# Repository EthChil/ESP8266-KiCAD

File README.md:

# ESP8266-KiCAD
Latest gerbers are in the folder plots. The files for the PCB are either the gerbers in plot or the pcb file.

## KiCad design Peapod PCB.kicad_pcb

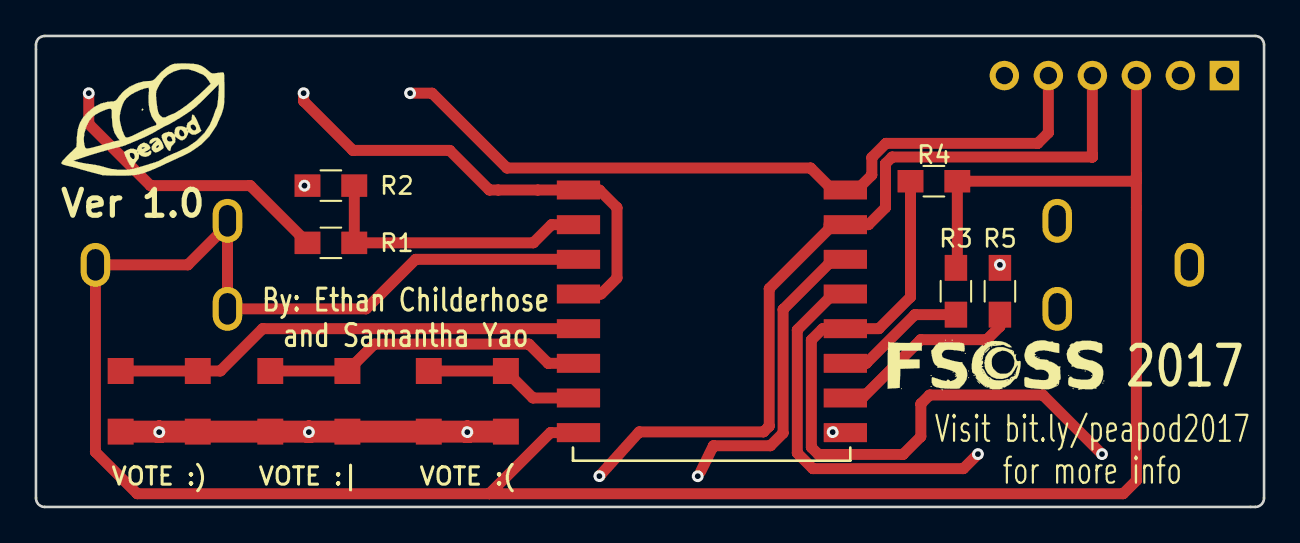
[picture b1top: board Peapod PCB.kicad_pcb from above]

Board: 2 copper layers, 70.9 x 27.2 mm, 18 parts (1 on the bottom side), 15 nets.

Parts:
ANALOG: CONN_01X01; Alligator Pad
BT1: Battery_Cell; BatteryMount
FTDI 3.3V: CONN_01X06; Pin_Header_Straight_1x06_Pitch2.54mm
GND   GPIO0: CONN_01X02; Bridge Pad
GPIO4, GPIO5: CONN_01X01; Alligator Pad
R1: 25k; R_0805_HandSoldering
R2, R3, R4, R5: 10k; R_0805_HandSoldering
RESET   GND: CONN_01X02; Bridge Pad
RX: CONN_01X01; Alligator Pad
TX: CONN_01X01; Alligator Pad
U1: ESP8266; ESP-12E_SMD
VOTE :(: Pushbutton
VOTE :): Pushbutton
VOTE :|: Pushbutton

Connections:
+3V3: BT1.1, FTDI 3.3V.3, R3.1, R4.2, U1.3, U1.8
GND: BT1.2, FTDI 3.3V.1, GND GPIO0.2, R2.2, R5.2, RESET GND.2, U1.9, VOTE :(.1, VOTE :).1, VOTE :|.1
unnamed: U1.6, VOTE :|.2
unnamed: U1.5, VOTE :).2
unnamed: U1.7, VOTE :(.2
unnamed: ANALOG.1, R1.2
unnamed: RESET GND.1, U1.1, U1.4
unnamed: FTDI 3.3V.4, RX.1, U1.15
unnamed: FTDI 3.3V.5, TX.1, U1.16
unnamed: GPIO5.1, U1.14
unnamed: GPIO4.1, U1.13
unnamed: GND GPIO0.1, R4.1, U1.12
unnamed: R1.1, R2.1, U1.2
unnamed: R3.2, U1.11
unnamed: R5.1, U1.10

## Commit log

2017-08-15 new KiCAD project
2017-08-15 Added bash files
2017-08-15 added button libs
2017-08-15 more libs
2017-08-15 deleted useless libs
2017-08-15 Added pushbutton
2017-08-15 Changed PushButton
2017-08-15 Updated PushButton
2017-08-15 finished schematic
2017-08-15 updated schematic
2017-08-15 Updated file
2017-08-15 Updated main file
2017-08-15 alligator pad done
2017-08-15 bridge pad made
2017-08-15 created battery mount
2017-08-16 assigned footprints
2017-08-16 finished assigning footprints to components
2017-08-16 fixed changes
2017-08-16 Changed Button
2017-08-16 centered footprints
2017-08-16 fixed battery mount
2017-08-16 Updated lib
2017-08-16 designing
2017-08-17 Changed main file for layout
2017-08-17 changed things
2017-08-17 made vias and tracks
2017-08-17 made fill zones
2017-08-17 fixed stuff
2017-08-17 Moved routing on the lines
2017-08-17 got rid of most vias
2017-08-17 Changed Via
2017-08-17 changed copper to back plate
2017-08-17 Changed schematic
2017-08-17 stuff
2017-08-17 stufff
2017-08-17 Added labels
2017-08-17 Updated tracks
2017-08-17 final??
2017-08-17 Made wire routes nicer
2017-08-17 looks nice
2017-08-17 Changed the routing again
2017-08-17 Changed one run
2017-08-17 Moved RX TX
2017-08-17 Moved RX TX up
2017-08-18 Updated via width
2017-08-18 Moved the vote images
2017-08-18 refilled
2017-08-18 old version
2017-08-18 Total re work
2017-08-18 Overwrite pt2
2017-08-18 updated runs
2017-08-18 Added keep out
2017-08-18 Moved zone outline
2017-08-18 Tuned the routing
2017-08-18 Moved Via
2017-08-18 Added gerbers and updated the silk screen
2017-08-19 Updated Pads
    Moved pads to the back layer
2017-08-21 silkscreens
2017-08-21 Updated pads
2017-08-21 finished labels
2017-08-21 fixed pad locations
2017-08-21 Moved Files
2017-08-21 Moved traces
2017-08-21 NO VIAS
2017-08-21 moved silkscreen
2017-08-21 moved vias
2017-08-21 moved things
2017-08-21 Final Board V1
2017-08-21 gerbers
2017-08-21 better gerbers
2017-09-01 Updated the Batt holes
